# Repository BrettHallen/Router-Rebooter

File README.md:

# Router Rebooter
Simple device to reboot my router when the NBN (National Broadband Network) stops working.<br>

This is typically when we're away from home for more than a week which means that the RING cameras & WiFi-enabled lights & powerpoints (to make it look like we're home) stop working.<br>

Yes, yes, I shouldn't be using cloud-enabled devices which will get bricked at the manufacturer's whim.  I'll work on it.<br>

And yes, there are devices that do this - they seemed a bit pricey.<br>

## Idea
The broadband router I have is a Netcomm Wireless NF18ACV that runs on 12VDC.  We got it when we originally had FTTN (fibre to the node) which runs optical fibre to a street cabinet/node and then uses the decades-old telephone copper cabling to the house.  Where we live now has FTTP (fibre to the premises) where the optical fibre runs straight to the house.  The same router still works fine so have never replaced it.<br>

I'll use an ESP32-type device to ping a reliable Internet address every minute, say a well-known DNS address like 1.1.1.1.  The ESP32 will be powered from the 12V input supply via a 5V regulator.  The power to the router will run through an NC (normally closed) relay.<br>

If there is no response for a few consecutive pings then I'll energise the relay which switches to open and disconnects the 12V to the router.<br>

After a short delay I'll then de-energise the relay and power the router back on.<br>

After another short delay whilst the router reconnects (2-3min) I'll reconnect to the WiFi network and resume pinging.

## YouTube Videos
- [Part 1: Initial build & test](https://youtu.be/Fz1aSylL9KQ)
- [Part 2: Revised PCB & Improved Firmware](https://youtu.be/78il7RK1qrU)

## Examples
This is how it works using the serial port output - here we simulate the loss of Internet by using dummy IP addresses:<br>
```
>> Brett's Router Rebooter Starting!
   (2/Apr/2026)
>> Monitoring NF18ACV
>> Timer/retry settings (DEBUG):
   Ping timer .......... 10s
   Ping retries ........ 3
   Ping retry timer .... 5s
   Power cycle timer ... 30s
   Recovery delay ...... 120s
>> Hardware initialised: Router on, OK LED on, FAILURE LED off, Ping LED off.
!! [handleHttpClients] WiFi not connected, ignoring HTTP requests.
>> Connecting to WiFi network <RouterRebootTest> ...
>> Using static IP address <192.168.128.129>
>> WiFi status = 3 (successfully connected!)
>> Connected to <RouterRebootTest> with address <192.168.128.129>
>> HTTP status page started on port 80
   Open in browser: http://192.168.128.129
>> Syncing NTP time (pool.ntp.org) ... 02/Apr/2026 18:53:07 (AEDT)
>> Pinging 1.1.1.1          Cloudflare primary   ... OK!
>> Pinging 192.168.123.123  Dummy test failure   ... failed!
>> Pinging 1.0.0.1          Cloudflare secondary ... OK!
>> Pinging 192.168.123.123  Dummy test failure   ... failed!
>> Pinging 192.168.123.123  Dummy test failure   ... failed!
>> Pinging 192.168.123.123  Dummy test failure   ... failed!
>> Pinging 192.168.123.123  Dummy test failure   ... failed!
!! No response after retries, disconnecting router power.
>> Waiting 30s before reconnecting power ...
   30s
   25s
   20s
   15s
   10s
   5s
>> Powering router back on.
>> Waiting 120s before resuming monitoring ...
   120s
   105s
   90s
   75s
   60s
   45s
   30s
   15s
>> Router recovery finished – resuming monitoring.

... and so on ...
```
And this is what it does when the Internet is fine, which should be 99.9% of the time:
```

>> Brett's Router Rebooter Starting!
   (2/Apr/2026)
>> Monitoring NF18ACV
>> Timer/retry settings:
   Ping timer .......... 1s
   Ping retries ........ 5
   Ping retry timer .... 15s
   Power cycle timer ... 30s
   Recovery delay ...... 180s
>> Hardware initialised: Router on, OK LED on, FAILURE LED off, Ping LED off.
!! [handleHttpClients] WiFi not connected, ignoring HTTP requests.
>> Connecting to WiFi network <RouterRebootTest> ...
>> Using static IP address <192.168.128.129>
>> WiFi status = 3 (successfully connected!)
>> Connected to <RouterRebootTest> with address <192.168.128.129>
>> HTTP status page started on port 80
   Open in browser: http://192.168.128.129
>> Syncing NTP time (pool.ntp.org) ... 02/Apr/2026 20:26:19 (AEDT)
>> Pinging 1.1.1.1          Cloudflare primary   ... OK!
>> Pinging 1.0.0.1          Cloudflare secondary ... OK!
>> Pinging 8.8.8.8          Google primary       ... OK!
>> Pinging 8.8.4.4          Google secondary     ... OK!
>> Pinging 9.9.9.9          Quad9 primary        ... OK!
>> Pinging 149.112.112.112  Quad9 secondary      ... OK!
>> Pinging 4.2.2.1          Level 3 primary      ... OK!
>> Pinging 4.2.2.2          Level 3 secondary    ... OK!
>> Pinging 4.2.2.3          Level 3 tertiary     ... OK!
>> Pinging 208.67.222.222   OpenDNS primary      ... OK!
>> Pinging 208.67.220.220   OpenDNS secondary    ... OK!
>> Pinging 1.1.1.1          Cloudflare primary   ... OK!
>> Pinging 1.0.0.1          Cloudflare secondary ... OK!
>> Pinging 8.8.8.8          Google primary       ... OK!
>> Pinging 8.8.4.4          Google secondary     ... OK!

... and so on ...
```

## [Firmware (Arduino Sketch)](/Firmware)
Use the Arduino IDE to compile & transfer to the ESP32.<br>

### Versions
- [Tested version](/Router-Rebooter)
- [Experimental version](/Experimental_version)

Experimental version - seems to be working fine, testing ongoing:<br>
- added support to ping IP addresses as well as FQDNs

### Required Libraries
Install via the Arduino IDE.
- [ESPping](https://github.com/dvarrel/ESPping)
- [Adafruit NeoPixel](https://github.com/adafruit/adafruit_neopixel)
- [Timezone](https://github.com/JChristensen/Timezone)

### Possible Improvements
- Send a message after the router has been rebooted (via CallMeBot to WhatsApp?)

## LED Status
There are three LEDs: the OK LED (suggested green), the FAILURE LED (suggested red) and the ESP32's built-in LED (RGB).<br>

| OK LED   | FAILURE LED | ESP32 LED           | Meaning                        |
|----------|-------------|---------------------|--------------------------------|
| On       | Off         | Green/blue flashing | Connecting to WiFi             |
| On       | Off         | Off                 | Everything ok, waiting to ping |
| On       | Off         | Blue pulse          | Pinging                        |
| On       | On          | Red                 | Ping failed                    |
| Off      | On          | Off                 | Ping retries failed            |
| Off      | On          | Green flashing      | Router power cycling           |
| Flashing | Flashing    | Red/green flashing  | Waiting for router to recover  |   

## Hardware
There's currently two versions:
- [Rev. B](/KiCad/RevB) minor corrections of my original design with 2.1mm DC sockets and vertically mounted regulator 
- [Rev. D](/KiCad/RevC) removes the 2.1mm DC sockets, lies the 5V regulator down and adds regulator output bypass for the ESP32 when connected via serial/USB

### Parts
- OMRON GL5E-1-VD relay (or similar)
- ESP32-C3-Zero development board (Waveshare)
- 10µF capacitor for the ESP32 power - could probably be left off (short pins)
- One 7805-type 5V regulator (i.e. [EzSBC's PSU2-5](https://ezsbc.shop/products/psu2-5-5v-1amp-three-pin-regulator)) to power the ESP. I am using a switching regulator so don't have any provision for heatsinking a linear regulator.
- Two 2.1mm DC power sockets to pass through the 12VDC
- Some other bits (2N2222 transistor, 1KΩ resistor, 1N4148 diode) to connect the relay coil to the ESP32
- 2-pin header to disconnect 5V regulator when ESP32 is connected to USB for testing to avoid connecting two power supplies
- Four M3 screws to mount it somehow

I've sized the PCB (62x49mm) to fit an 83x54x31mm Jiffy Box [(Jaycar HB6015)](https://www.jaycar.com.au/jiffy-box-black-83-x-54-x-31mm/p/HB6015).<br>

Waveshare ESP32-C3-Zero symbol/footprint/3D model from:<br>
https://github.com/jonathanadams/KiCad-Waveshare-ESP32

## Images
### Rev A. version built
The green OK LED indicates normal operation of the router and the blue ESP32 LED indicates it's currently sending a test ping to test reachability.

### Rev. C version 3D rendering

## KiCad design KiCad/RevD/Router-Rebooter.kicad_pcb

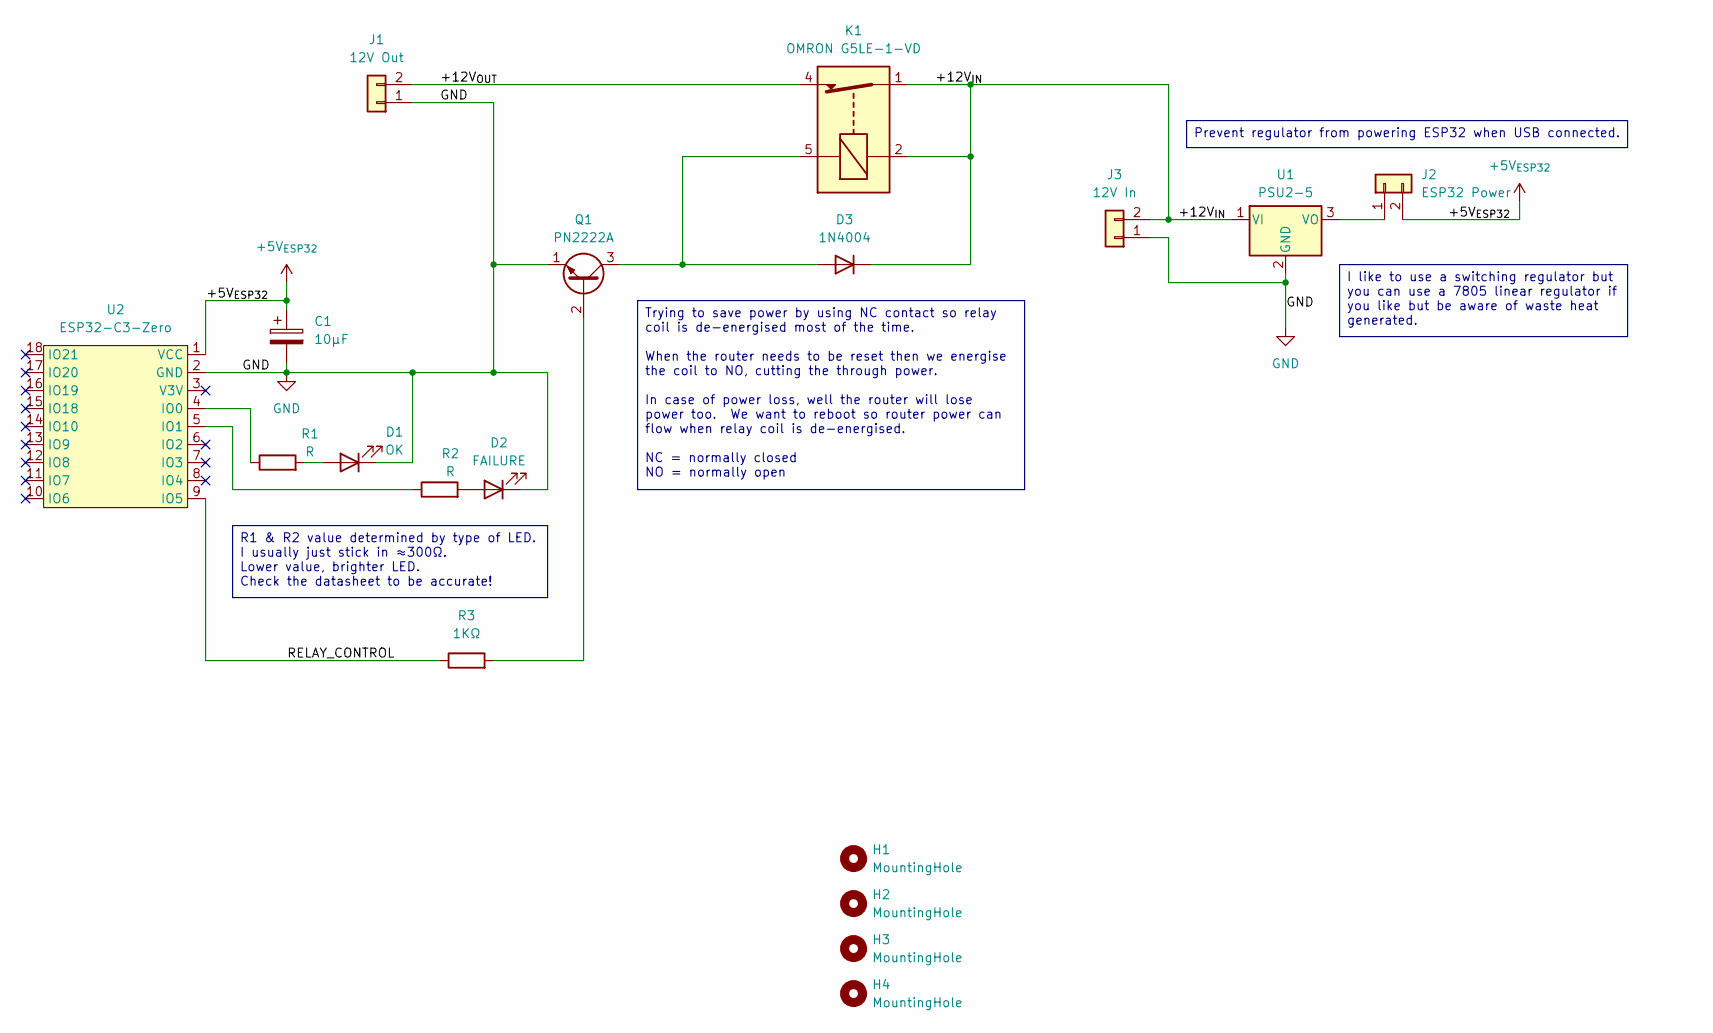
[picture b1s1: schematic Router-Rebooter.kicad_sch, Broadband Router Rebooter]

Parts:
C1: 10µF; CP_Radial_D5.0mm_P2.50mm
D1: OK; LED_D3.0mm
D2: FAILURE; LED_D3.0mm
D3: 1N4004; D_DO-41_SOD81_P10.16mm_Horizontal
H1, H2, H3, H4: MountingHole; MountingHole_3.2mm_M3_DIN965
J1: 12V Out; PinHeader_1x02_P2.54mm_Vertical
J2: ESP32 Power; PinHeader_1x02_P2.54mm_Vertical
J3: 12V In; PinHeader_1x02_P2.54mm_Vertical
K1: OMRON G5LE-1-VD; Relay_SPDT_Omron-G5LE-1
Q1: PN2222A; TO-92_Inline
R1, R2: R; R_Axial_DIN0207_L6.3mm_D2.5mm_P7.62mm_Horizontal
R3: 1KΩ; R_Axial_DIN0207_L6.3mm_D2.5mm_P7.62mm_Horizontal
U1: PSU2-5; TO-220-3_Horizontal_TabDown
U2: ESP32-C3-Zero; Waveshare-ESP32-C3-Zero

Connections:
+5V_{ESP32}: C1.1, J2.2, U2.1 (VCC)
/+12V_{IN}: D3.1 (K), J3.2, K1.1, K1.2, U1.1 (VI)
/+12V_{OUT}: J1.2, K1.4
/RELAY_CONTROL: R3.1, U2.9 (IO5)
GND: C1.2, D1.1 (K), D2.1 (K), J1.1, J3.1, Q1.1 (E), U1.2 (GND), U2.2 (GND)
unnamed: D1.2 (A), R1.2
unnamed: D2.2 (A), R2.2
unnamed: D3.2 (A), K1.5, Q1.3 (C)
unnamed: J2.1, U1.3 (VO)
unnamed: Q1.2 (B), R3.2
unnamed: R1.1, U2.4 (IO0)
unnamed: R2.1, U2.5 (IO1)

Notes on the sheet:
R1 & R2 value determined by type of LED. I usually just stick in ≈300Ω. Lower value, brighter LED. Check the datasheet to be accurate!
I like to use a switching regulator but you can use a 7805 linear regulator if you like but be aware of waste heat generated.
Prevent regulator from powering ESP32 when USB connected.
Trying to save power by using NC contact so relay coil is de-energised most of the time. When the router needs to be reset then we energise the coil to NO, cutting the through power. In case of power loss, well the router will lose power too. We want to reboot so router power can flow when relay co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

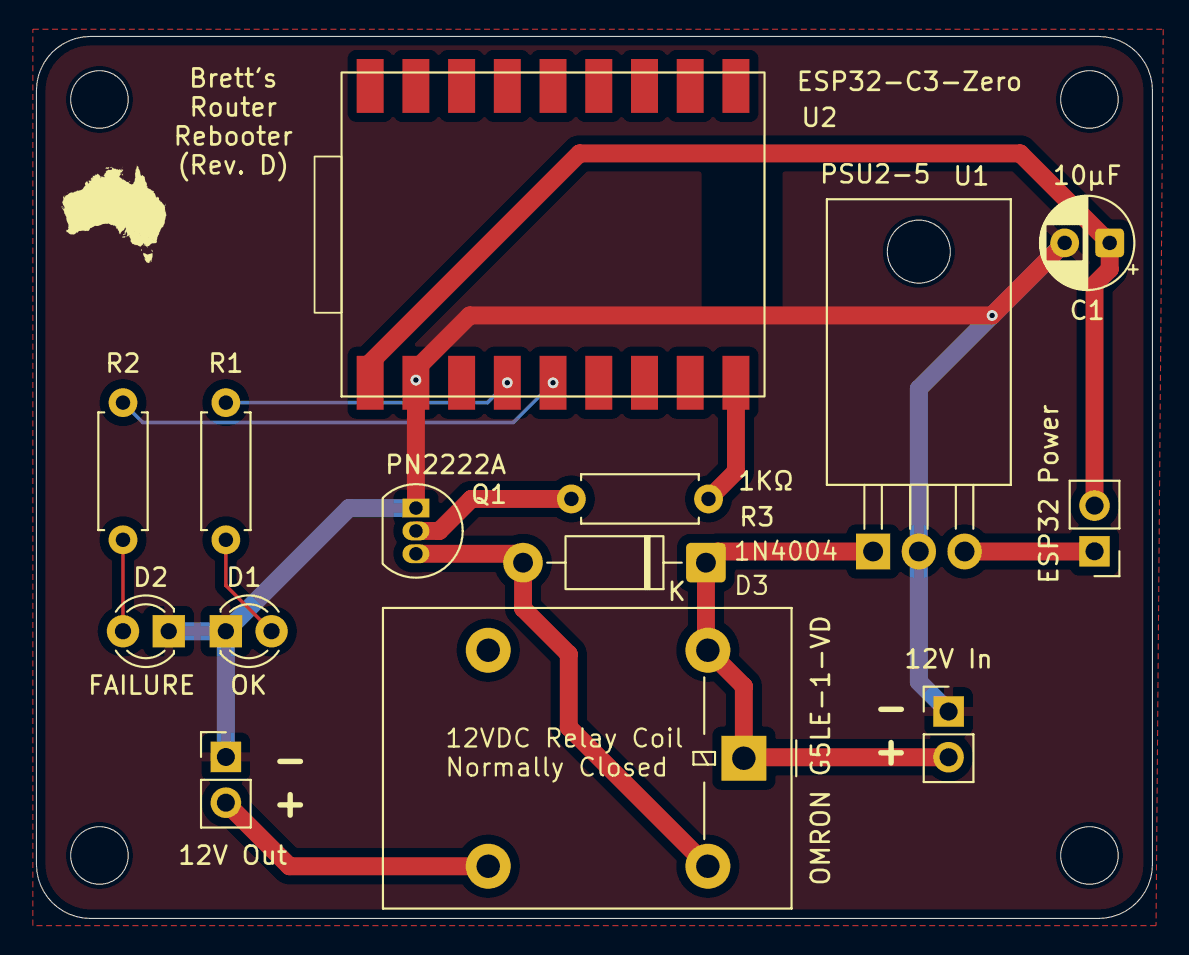
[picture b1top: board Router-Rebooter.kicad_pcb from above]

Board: 2 copper layers, 62.0 x 49.0 mm, 18 parts (0 on the bottom side), 12 nets.

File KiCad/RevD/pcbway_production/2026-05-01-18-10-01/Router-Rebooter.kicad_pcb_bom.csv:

Designator,Quantity,Value,Footprint,Package,MPN,DNP,Mount_Type,Description,Sim.Pins,Sim.Device
C1,1,10µF,CP_Radial_D5.0mm_P2.50mm,,,,tht,Polarized capacitor,,
D1,1,OK,LED_D3.0mm,,,,tht,Light emitting diode,1=K 2=A,
D2,1,FAILURE,LED_D3.0mm,,,,tht,Light emitting diode,1=K 2=A,
D3,1,1N4004,D_DO-41_SOD81_P10.16mm_Horizontal,,,,tht,Diode,1=K 2=A,D
J1,1,12V Out,PinHeader_1x02_P2.54mm_Vertical,,,,tht,"Generic connector, single row, 01x02, script generated (kicad-library-utils/schlib/autogen/connector/)",,
J2,1,ESP32 Power,PinHeader_1x02_P2.54mm_Vertical,,,,tht,"Generic connector, single row, 01x02, script generated (kicad-library-utils/schlib/autogen/connector/)",,
J3,1,12V In,PinHeader_1x02_P2.54mm_Vertical,,,,tht,"Generic connector, single row, 01x02, script generated (kicad-library-utils/schlib/autogen/connector/)",,
K1,1,OMRON G5LE-1-VD,Relay_SPDT_Omron-G5LE-1,,,,tht,"Sanyo SRD relay, Single Pole Miniature Power Relay, Opening Contact",,
Q1,1,PN2222A,TO-92_Inline,,,,tht,"1A Ic, 40V Vce, NPN Transistor, General Purpose Transistor, TO-92",,
"R1, R2",2,R,R_Axial_DIN0207_L6.3mm_D2.5mm_P7.62mm_Horizontal,,,,tht,Resistor,,
R3,1,1KΩ,R_Axial_DIN0207_L6.3mm_D2.5mm_P7.62mm_Horizontal,,,,tht,Resistor,,
U1,1,PSU2-5,TO-220-3_Horizontal_TabDown,,,,tht,"Positive 1A 35V Linear Regulator, Fixed Output 5V, TO-220",,
U2,1,ESP32-C3-Zero,Waveshare-ESP32-C3-Zero,,,,smt,,,

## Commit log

2026-01-22 Added indicator LEDs (OK & FAILURE)
    OK is steady green when everything is okay
    FAILURE is flashing red when rebooting
2026-03-26 Initial built version for testing
2026-03-26 Cosmetic changes
2026-03-26 Initial version of ESP32-C3-Zero code
2026-03-27 Corrected schematic/footprint errors
2026-03-27 Tested sketch
2026-03-27 Tested relay
2026-03-27 Added round-robin target IP address list
2026-03-27 Updated 3D image
2026-03-27 Folder re-org
2026-03-27 Added ESP32 LED activity & DEBUG_MODE conditional
2026-03-27 Updated REV and date
2026-03-27 Modified component IDs to match
    Now R1 is for LED D1, R2 is for LED D2
2026-03-27 Moved to Rev. B folder
2026-03-27 Major redesign as Rev. C
2026-03-27 Removed 3D model for 12V pin headers
2026-03-27 Rev. C image
2026-03-27 Added ESP32 LED activity & DEBUG_MODE flag
2026-03-28 Added WiFi status print to debug
2026-03-28 Small PCB adjustments
2026-03-29 Added static IP & status web page
2026-03-29 Type correction
2026-03-29 Added ESP32 uptime statistic
2026-03-29 Re-oriented the PCB
2026-03-30 Added DNS name list to output
2026-03-30 Added NTP timekeeping
    BUT ... there is a kernel panic during debug testing after power is cycled and wifi disconnect/reconnects ... suspect it might be due to HTTP GET requests
2026-03-30 Added last failed ping timestamp to HTTP status page
2026-03-30 Resolved kernel panic after router reboot phase
    - Also cleaned up the code, tried to add useful comments everywhere
    - added use of F() to preserve RAM/heap usage
2026-03-30 Modified blinkenlites
2026-04-01 Added Github repo link to status page
2026-04-02 Updated from experimental vers (1-Apr-2026)
2026-04-02 Added TZ & DST handling
2026-04-02 Added TZ/DST handling plus status page updates
2026-04-02 Additional timestamp validity checking
2026-04-03 Added first NTP sync bool
    Need to avoid invalid 1/Jan/1970 timestamps ... really, the reboot/ping failure timestamp can't be any sooner than right now ... they can't be 1970, they can't be 2000, they can't be March 2026 ...
    Also added some padding/fixed width to the serial output logs just to make things look a bit nicer
2026-04-05 Added reboot count & other minor tweaks
2026-04-12 Artwork update
2026-04-15 Replaced D3, added D4
2026-04-16 Fixed UTC-local TZ bug for failed pings
2026-04-20 Updated experimental version to tested version
2026-04-20 Added user text to PCB
    Clarify the empty zone on PCB is where the ESP32's WiFi antenna is so should be kept clear (this is for the PCB fab)
2026-04-30 Moved LED resistors to fix USB-C access to ESP32
2026-05-01 Modified ESP32 power bypass
    The ESP32 serial via USB wouldn't connect if the board was already powered via 12V - had to connect via USB first and then apply 12V power.
    So let's just have a simple 2-pin header to connect or disconnect the 5V regulator from the ESP32.
2026-05-02 Reachability typo
    Thanks Brian
2026-05-02 Updated from experimental version
    [1] Swapped d/m/y h:m:s to h:m:s d/m/y
    [2] Fixed Re(a)chability typo (thanks Brian)
2026-05-03 Ping IP addresses & FQDNs
2026-05-27 Added FQDN pinging
